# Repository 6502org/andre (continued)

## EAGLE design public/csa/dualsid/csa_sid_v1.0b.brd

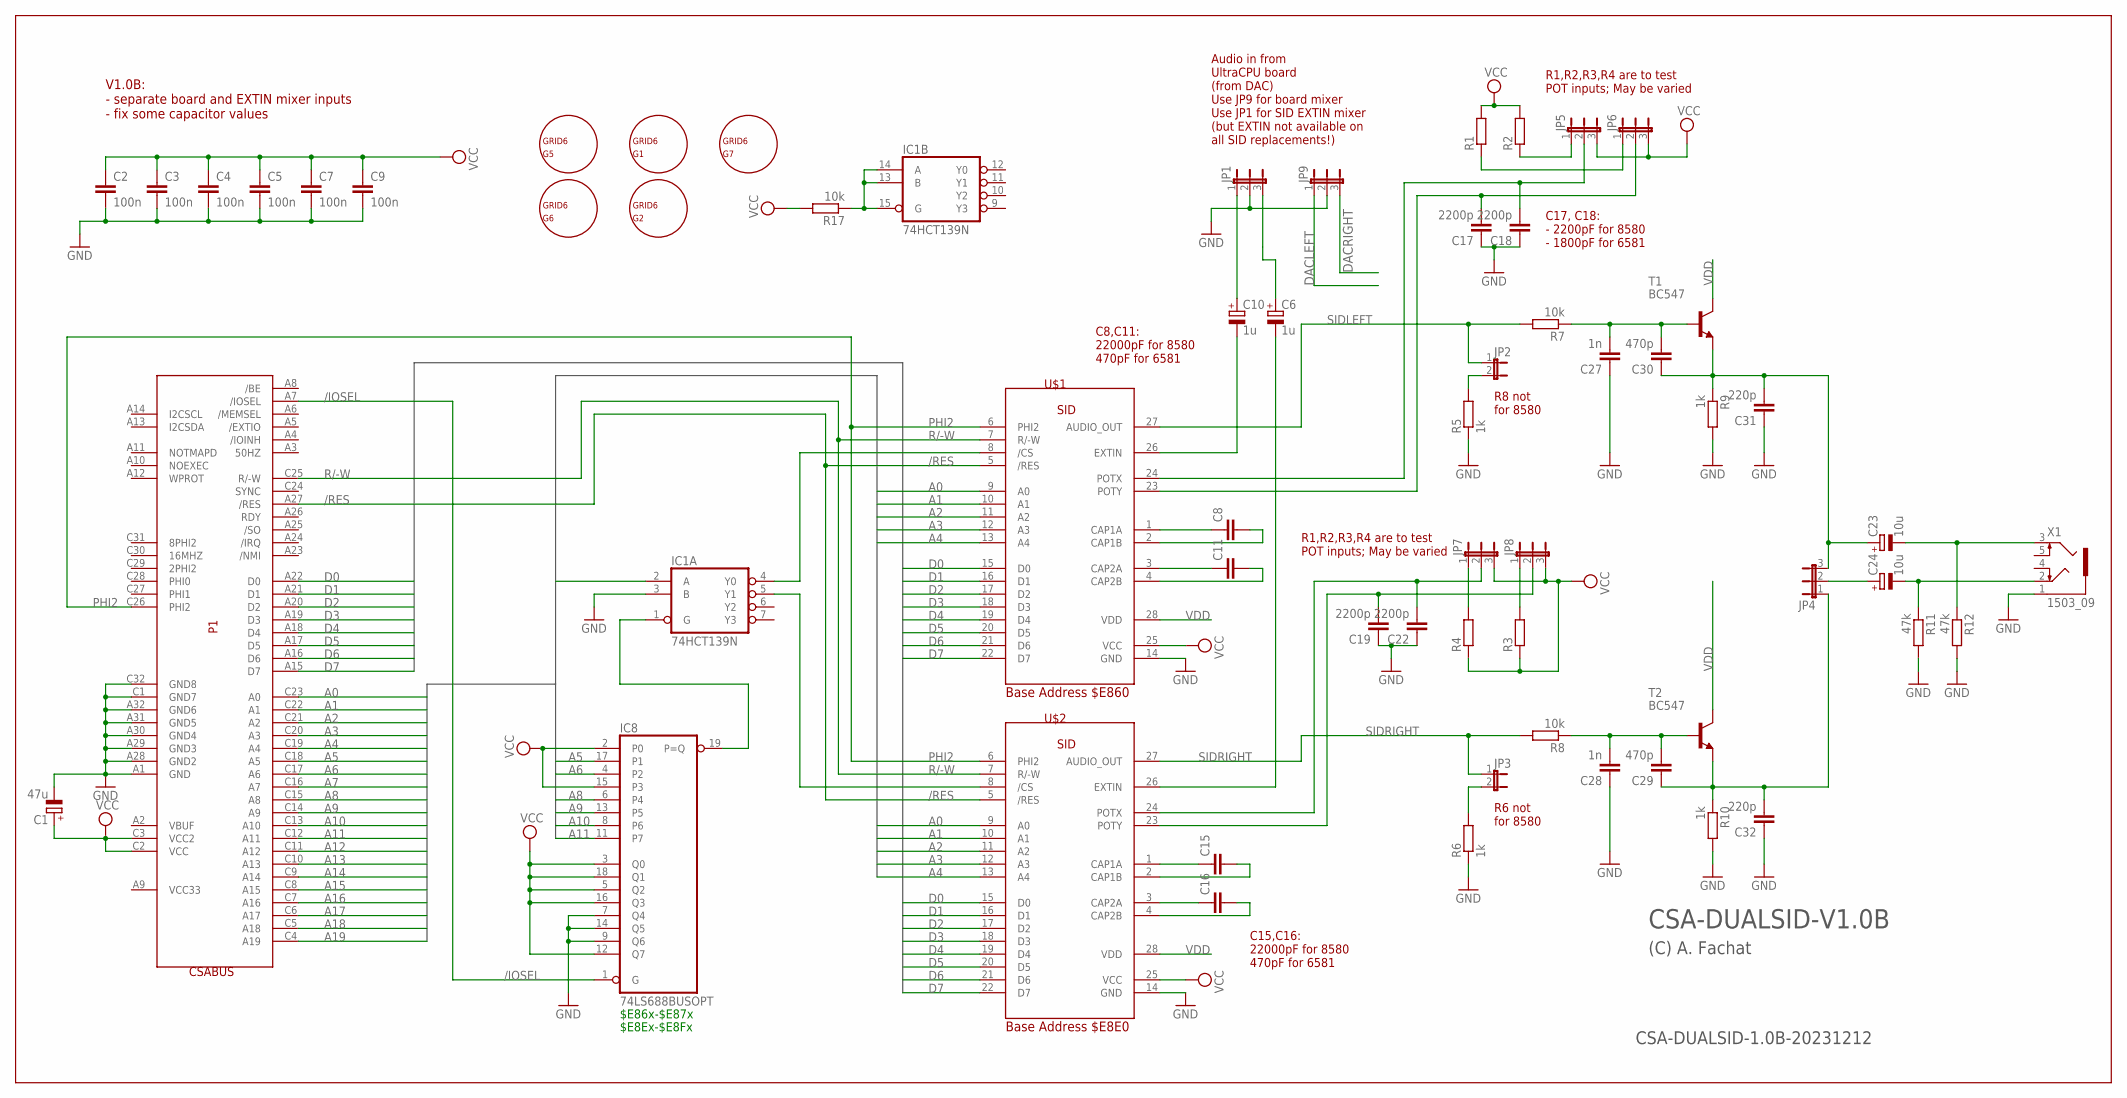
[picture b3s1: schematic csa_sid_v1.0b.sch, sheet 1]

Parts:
C1: 47u; E2,5-7
C2, C3, C4, C5, C7, C9: 100n; C025-025X050
C6, C10: 1u; E2-5
C8, C11, C15, C16: C-EU025-025X050; C025-025X050
C17, C18, C19, C22: 2200p; C025-025X050
C23, C24: 10u; E2-5
C27, C28: 1n; C025-025X050
C29, C30: 470p; C025-025X050
C31, C32: 220p; C025-025X050
G1, G2, G5, G6, G7: GRID6
IC1: 74HCT139N; DIL16
IC8: 74LS688BUSOPT; DIL20
JP1, JP4, JP5, JP6, JP7, JP8, JP9: JP2E; JP2
JP2, JP3: JP1E; JP1
P1: CSABUS
R1, R2, R3, R4: R-EU_0204/7; 0204/7
R5, R6, R9, R10: 1k; 0204/7
R7, R8, R17: 10k; 0204/7
R11, R12: 47k; 0204/7
T1, T2: BC547; TO92
U$1, U$2: SID; DIL28
X1: 1503_09

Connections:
/IOSEL: IC8.1 (G), P1.A7 (/IOSEL)
/RES: P1.A27 (/RES), U$1.5 (/RES), U$2.5 (/RES)
A0: P1.C23 (A0), U$1.9 (A0), U$2.9 (A0)
A1: P1.C22 (A1), U$1.10 (A1), U$2.10 (A1)
A2: P1.C21 (A2), U$1.11 (A2), U$2.11 (A2)
A3: P1.C20 (A3), U$1.12 (A3), U$2.12 (A3)
A4: P1.C19 (A4), U$1.13 (A4), U$2.13 (A4)
A5: IC8.17 (P1), P1.C18 (A5)
A6: IC8.4 (P2), P1.C17 (A6)
A7: IC1.2 (A), P1.C16 (A7)
A8: IC8.6 (P4), P1.C15 (A8)
A9: IC8.13 (P5), P1.C14 (A9)
A10: IC8.8 (P6), P1.C13 (A10)
A11: IC8.11 (P7), P1.C12 (A11)
A12: P1.C11 (A12)
A13: P1.C10 (A13)
A14: P1.C9 (A14)
A15: P1.C8 (A15)
A16: P1.C7 (A16)
A17: P1.C6 (A17)
A18: P1.C5 (A18)
A19: P1.C4 (A19)
D0: P1.A22 (D0), U$1.15 (D0), U$2.15 (D0)
D1: P1.A21 (D1), U$1.16 (D1), U$2.16 (D1)
D2: P1.A20 (D2), U$1.17 (D2), U$2.17 (D2)
D3: P1.A19 (D3), U$1.18 (D3), U$2.18 (D3)
D4: P1.A18 (D4), U$1.19 (D4), U$2.19 (D4)
D5: P1.A17 (D5), U$1.20 (D5), U$2.20 (D5)
D6: P1.A16 (D6), U$1.21 (D6), U$2.21 (D6)
D7: P1.A15 (D7), U$1.22 (D7), U$2.22 (D7)
DACLEFT: JP9.1; also elsewhere on the board
DACRIGHT: JP9.3; also elsewhere on the board
GND: C1.-, C2.2, C3.2, C4.2, C5.2, C7.2, C9.2, C17.1, C18.1, C19.1, C22.1, C27.1, C28.1, C31.1, C32.1, IC1.3 (B), IC1.8 (GND), IC8.7 (Q4), IC8.9 (Q6), IC8.10 (GND), IC8.14 (Q5), JP1.2, JP9.2, P1.A1 (GND), P1.A28 (GND2), P1.A29 (GND3), P1.A30 (GND4), P1.A31 (GND5), P1.A32 (GND6), P1.C1 (GND7), P1.C32 (GND8), R5.1, R6.1, R9.2, R10.2, R11.2, R12.2, U$1.14 (GND), U$2.14 (GND), X1.1; also elsewhere on the board
unnamed: IC1.1 (G), IC8.19 (P=Q)
unnamed: IC1.4 (Y0), U$1.8 (/CS)
unnamed: IC1.5 (Y1), U$2.8 (/CS)
unnamed: C8.1, U$1.1 (CAP1A)
unnamed: C11.1, U$1.3 (CAP2A)
unnamed: C8.2, U$1.2 (CAP1B)
unnamed: C11.2, U$1.4 (CAP2B)
unnamed: C15.1, U$2.1 (CAP1A)
unnamed: C16.1, U$2.3 (CAP2A)
unnamed: C15.2, U$2.2 (CAP1B)
unnamed: C16.2, U$2.4 (CAP2B)
unnamed: C17.2, JP6.2, U$1.23 (POTY)
unnamed: C18.2, JP5.2, U$1.24 (POTX)
unnamed: C19.2, JP8.2, U$2.23 (POTY)
unnamed: C22.2, JP7.2, U$2.24 (POTX)
unnamed: C10.-, U$1.26 (EXTIN)
unnamed: JP5.1, R2.1
unnamed: JP6.1, R1.1
unnamed: JP3.2, R6.2
unnamed: JP2.2, R5.2
unnamed: C6.-, U$2.26 (EXTIN)
unnamed: C23.-, R12.1, X1.3
unnamed: C24.-, R11.1, X1.2
unnamed: C29.1, C32.2, JP4.1, R10.1, T2.1 (E)
unnamed: C23.+, C30.1, C31.2, JP4.3, R9.1, T1.1 (E)
unnamed: C27.2, C30.2, R7.1, T1.2 (B)
unnamed: C28.2, C29.2, R8.1, T2.2 (B)
unnamed: C24.+, JP4.2
unnamed: IC1.13 (B), IC1.14 (A), IC1.15 (G), R17.1
unnamed: JP7.1, R4.2
unnamed: JP8.1, R3.2
unnamed: C6.+, JP1.3
unnamed: C10.+, JP1.1
PHI2: P1.C26 (PHI2), U$1.6 (PHI2), U$2.6 (PHI2)
R/-W: P1.C25 (R/-W), U$1.7 (R/-W), U$2.7 (R/-W)
SIDLEFT: JP2.1, R7.2, U$1.27 (AUDIO_OUT); also elsewhere on the board
SIDRIGHT: JP3.1, R8.2, U$2.27 (AUDIO_OUT); also elsewhere on the board
VCC: C1.+, C2.1, C3.1, C4.1, C5.1, C7.1, C9.1, IC1.16 (VCC), IC8.2 (P0), IC8.3 (Q0), IC8.5 (Q2), IC8.12 (Q7), IC8.15 (P3), IC8.16 (Q3), IC8.18 (Q1), IC8.20 (VCC), JP5.3, JP6.3, JP7.3, JP8.3, P1.C2 (VCC), P1.C3 (VCC2), R1.2, R2.2, R3.1, R4.1, R17.2, U$1.25 (VCC), U$2.25 (VCC); also elsewhere on the board
VDD: T1.3 (C), T2.3 (C), U$1.28 (VDD), U$2.28 (VDD); also elsewhere on the board

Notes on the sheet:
CSA-DUALSID-V1.0B
(C) A. Fachat
CSA-DUALSID-1.0B-20231212
$E86x-$E87x
$E8Ex-$E8Fx
Audio in from UltraCPU board (from DAC) Use JP9 for board mixer Use JP1 for SID EXTIN mixer (but EXTIN not available on all SID replacements!)
R8 not for 8580
R6 not for 8580
C8,C11: 22000pF for 8580 470pF for 6581
C15,C16: 22000pF for 8580 470pF for 6581
R1,R2,R3,R4 are to test POT inputs; May be varied
C17, C18: - 2200pF for 8580 - 1800pF for 6581
V1.0B: - separate board and EXTIN mixer inputs - fix some capacitor values
Base Address $E860
Base Address $E8E0

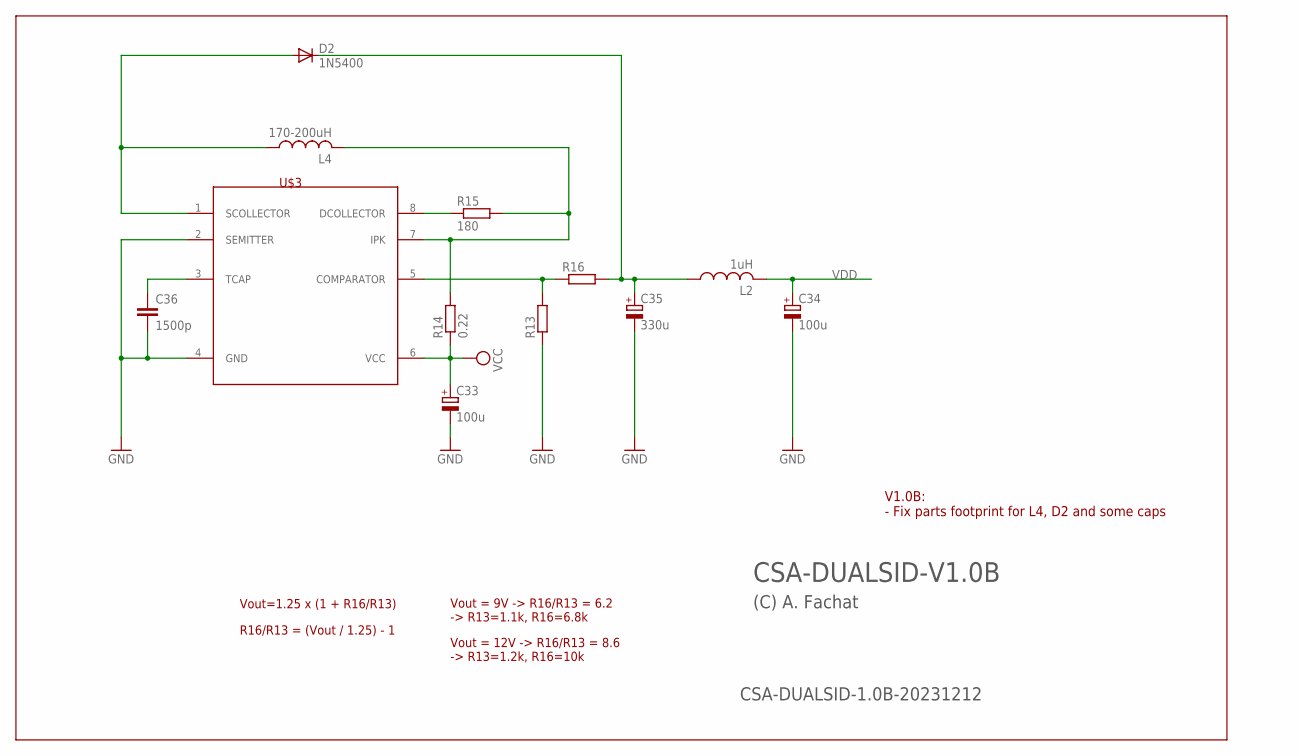
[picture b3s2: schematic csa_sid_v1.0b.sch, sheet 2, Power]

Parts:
C33, C34: 100u; E2,5-7
C35: 330u; E2,5-7
C36: 1500p; C025-024X044
D2: 1N5400; DO201-15
L2: 1uH; 0204/7
L4: 170-200uH; TJ4-U2
R13, R16: R-EU_0204/7; 0204/7
R14: 0.22; 0204/7
R15: 180; 0204/7
U$3: MC34063A; DIL08

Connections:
GND: C33.-, C34.-, C35.-, C36.2, R13.1, U$3.2 (SEMITTER), U$3.4 (GND); also elsewhere on the board
unnamed: C36.1, U$3.3 (TCAP)
unnamed: R13.2, R16.1, U$3.5 (COMPARATOR)
unnamed: D2.A, L4.1, U$3.1 (SCOLLECTOR)
unnamed: C35.+, D2.C, L2.1, R16.2
unnamed: L4.2, R14.2, R15.2, U$3.7 (IPK)
unnamed: R15.1, U$3.8 (DCOLLECTOR)
VCC: C33.+, R14.1, U$3.6 (VCC); also elsewhere on the board
VDD: C34.+, L2.2; also elsewhere on the board

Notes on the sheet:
Vout=1.25 x (1 + R16/R13)
R16/R13 = (Vout / 1.25) - 1
Vout = 9V -> R16/R13 = 6.2 -> R13=1.1k, R16=6.8k
Vout = 12V -> R16/R13 = 8.6 -> R13=1.2k, R16=10k
CSA-DUALSID-V1.0B
(C) A. Fachat
CSA-DUALSID-1.0B-20231212
V1.0B: - Fix parts footprint for L4, D2 and some caps

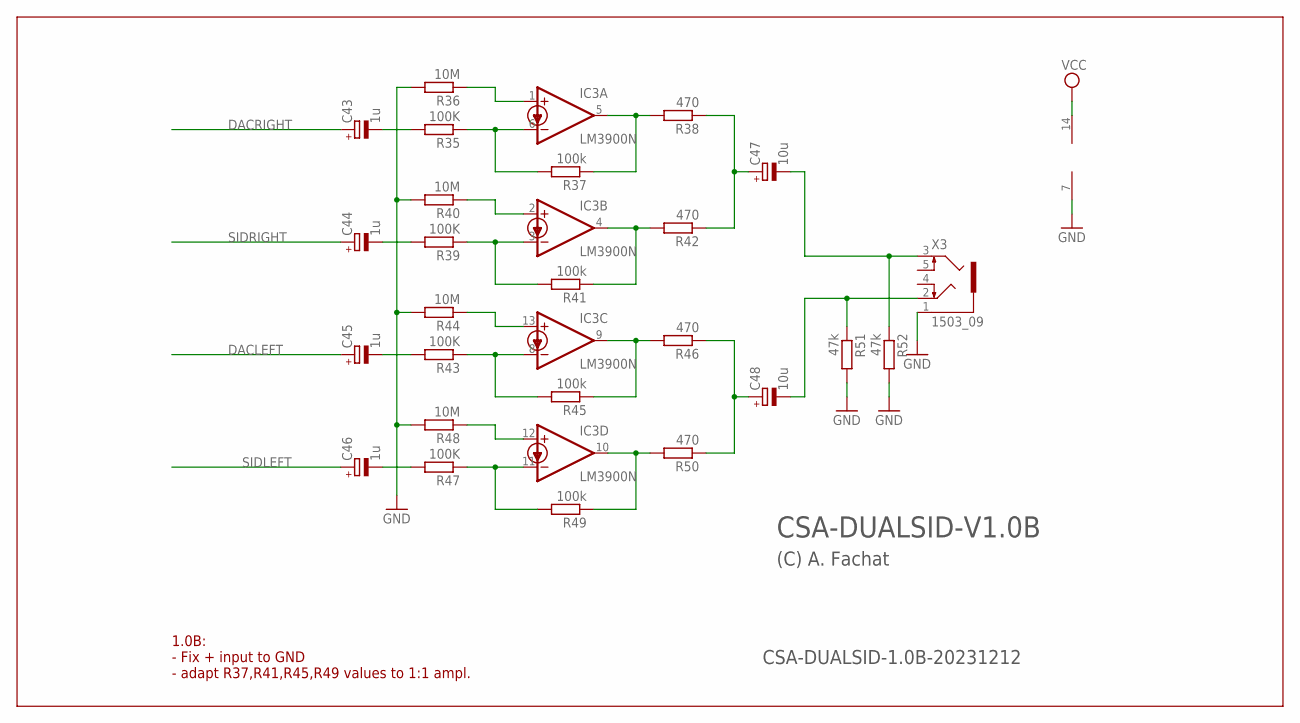
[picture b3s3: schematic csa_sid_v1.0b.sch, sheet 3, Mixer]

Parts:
C43, C44, C45, C46: 1u; E2-5
C47, C48: 10u; E2-5
IC3: LM3900N; DIL14
R35, R39, R43, R47: 100K; 0204/7
R36, R40, R44, R48: 10M; 0204/7
R37, R41, R45, R49: 100k; 0204/7
R38, R42, R46, R50: 470; 0204/7
R51, R52: 47k; 0204/7
X3: 1503_09

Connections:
DACLEFT: C45.+; also elsewhere on the board
DACRIGHT: C43.+; also elsewhere on the board
GND: IC3.7 (GND), R36.2, R40.2, R44.2, R48.2, R51.2, R52.2, X3.1; also elsewhere on the board
unnamed: IC3.1 (+IN), R36.1
unnamed: C43.-, R35.2
unnamed: IC3.6 (-IN), R35.1, R37.2
unnamed: IC3.5 (OUT), R37.1, R38.2
unnamed: IC3.2 (+IN), R40.1
unnamed: C44.-, R39.2
unnamed: IC3.3 (-IN), R39.1, R41.2
unnamed: IC3.4 (OUT), R41.1, R42.2
unnamed: IC3.13 (+IN), R44.1
unnamed: C45.-, R43.2
unnamed: IC3.8 (-IN), R43.1, R45.2
unnamed: IC3.9 (OUT), R45.1, R46.2
unnamed: IC3.12 (+IN), R48.1
unnamed: C46.-, R47.2
unnamed: IC3.11 (-IN), R47.1, R49.2
unnamed: IC3.10 (OUT), R49.1, R50.2
unnamed: C47.+, R38.1, R42.1
unnamed: C47.-, R52.1, X3.3
unnamed: C48.+, R46.1, R50.1
unnamed: C48.-, R51.1, X3.2
SIDLEFT: C46.+; also elsewhere on the board
SIDRIGHT: C44.+; also elsewhere on the board
VCC: IC3.14 (V+); also elsewhere on the board

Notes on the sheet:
CSA-DUALSID-V1.0B
(C) A. Fachat
CSA-DUALSID-1.0B-20231212
1.0B: - Fix + input to GND - adapt R37,R41,R45,R49 values to 1:1 ampl.

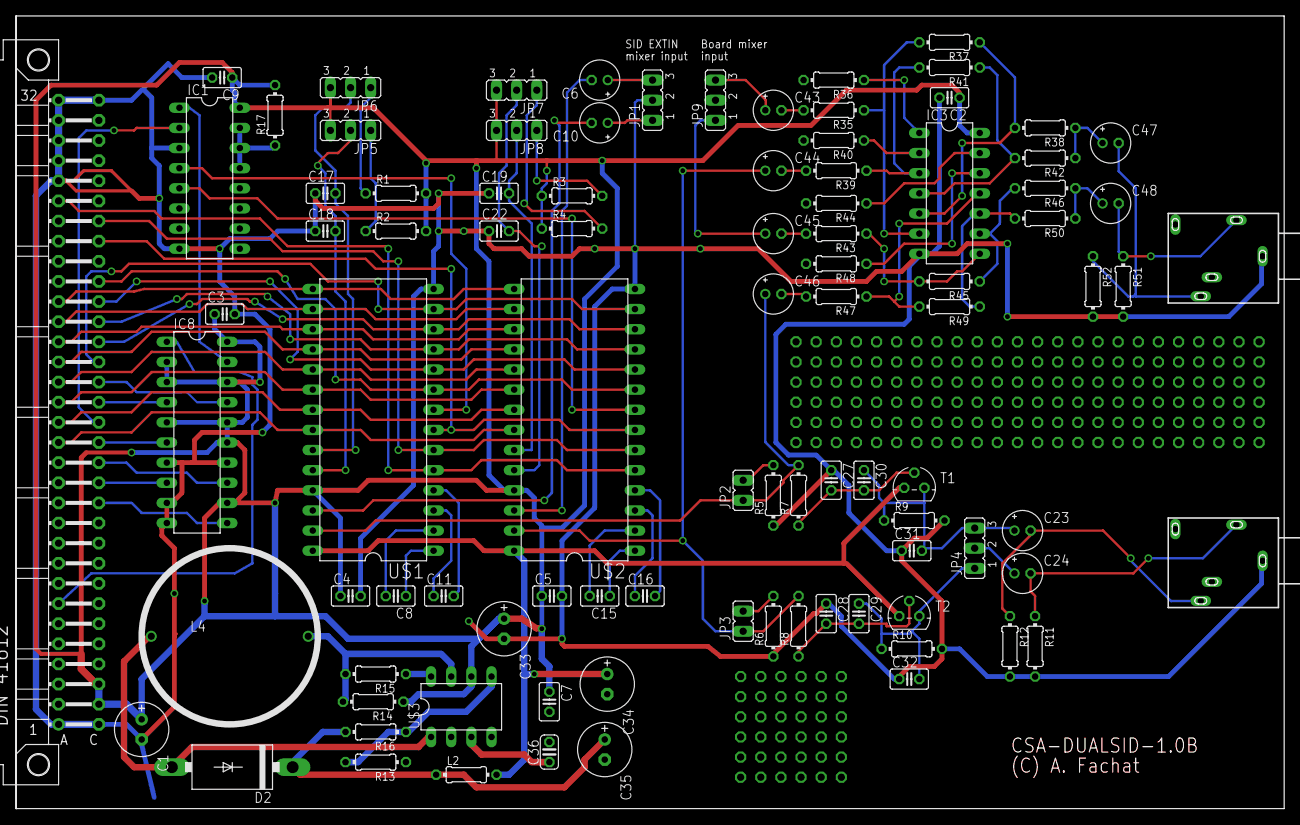
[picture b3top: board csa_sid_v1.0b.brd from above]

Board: 2 copper layers, 160.0 x 100.0 mm, 98 parts (0 on the bottom side), 90 nets.

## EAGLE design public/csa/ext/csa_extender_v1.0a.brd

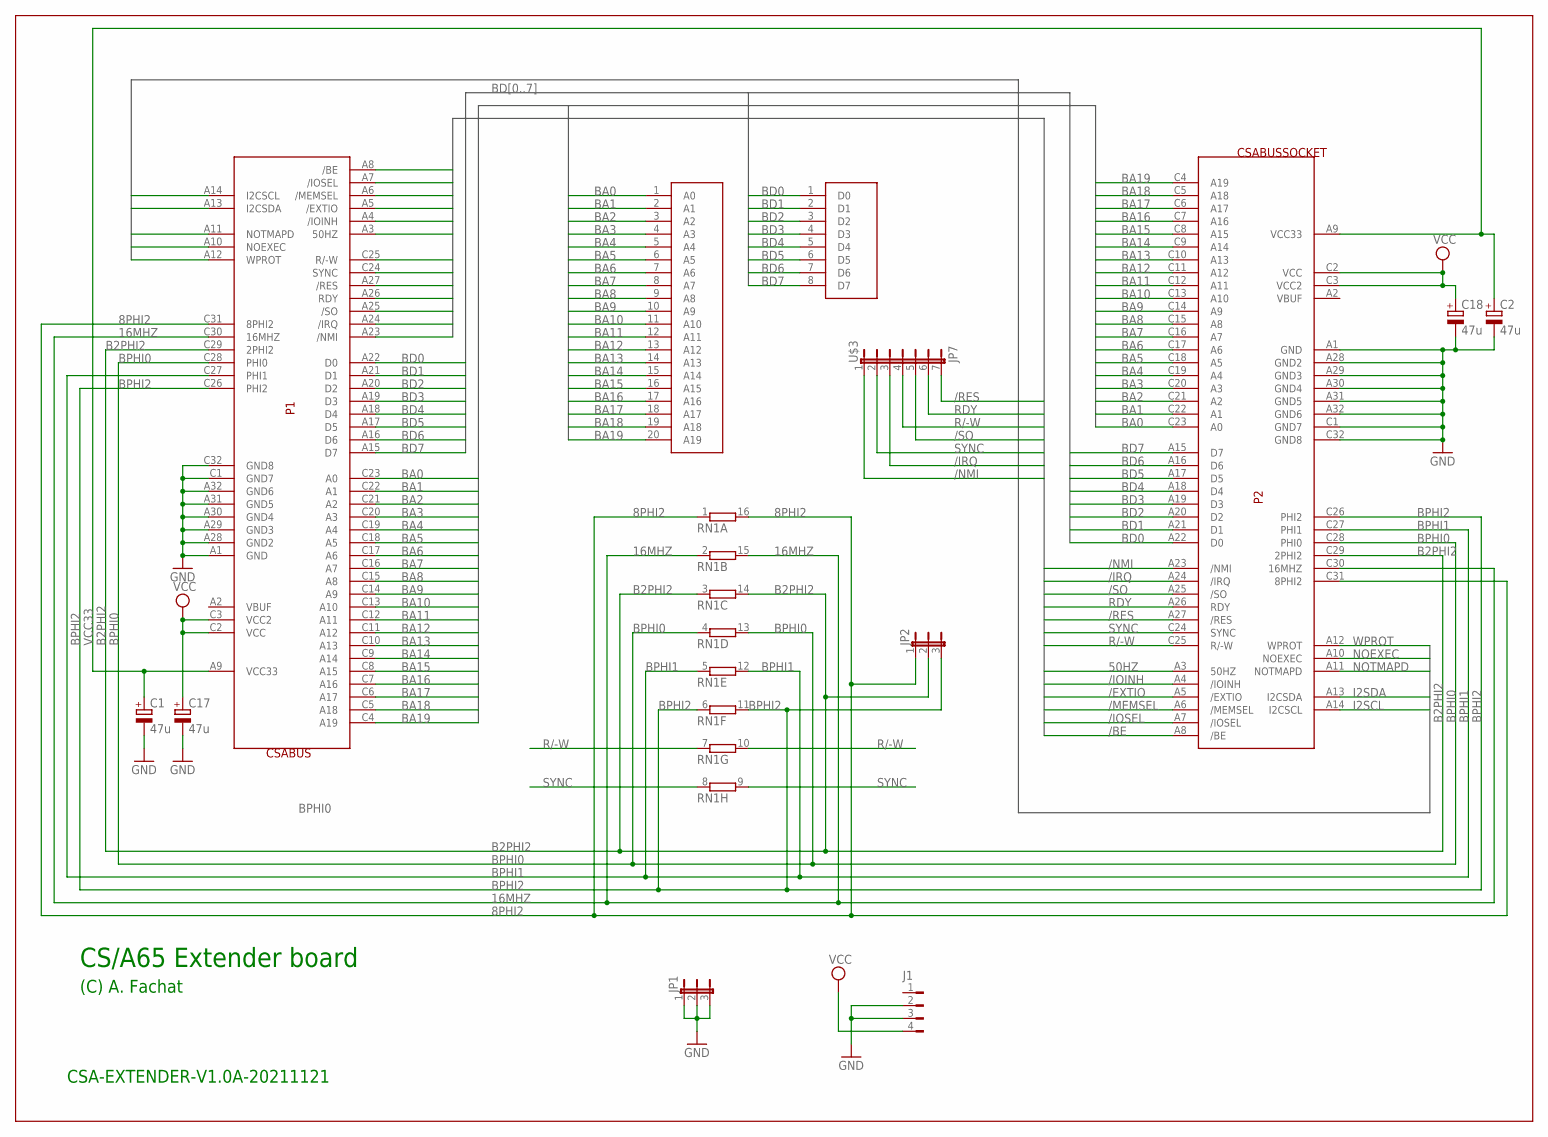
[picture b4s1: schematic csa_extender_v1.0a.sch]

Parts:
C1, C2, C17, C18: 47u; E2,5-5
J1: FLOP-4W827001; 827001
JP1, JP2: JP2E; JP2
P1: CSABUS
P2: CSABUSSOCKET; CSABUSSOCK
RN1: 8R-N; DIL16
U$1: JA0-19; A0-19
U$2: JD0-7; D0-7
U$3: JP7

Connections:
8PHI2: JP2.1, P1.C31 (8PHI2), P2.C31 (8PHI2), RN1.1, RN1.16 (2)
16MHZ: P1.C30 (16MHZ), P2.C30 (16MHZ), RN1.2 (1), RN1.15 (2)
50HZ: P1.A3 (50HZ), P2.A3 (50HZ)
/BE: P1.A8 (/BE), P2.A8 (/BE)
/EXTIO: P1.A5 (/EXTIO), P2.A5 (/EXTIO)
/IOINH: P1.A4 (/IOINH), P2.A4 (/IOINH)
/IOSEL: P1.A7 (/IOSEL), P2.A7 (/IOSEL)
/IRQ: P1.A24 (/IRQ), P2.A24 (/IRQ), U$3.3
/MEMSEL: P1.A6 (/MEMSEL), P2.A6 (/MEMSEL)
/NMI: P1.A23 (/NMI), P2.A23 (/NMI), U$3.1
/RES: P1.A27 (/RES), P2.A27 (/RES), U$3.7
/SO: P1.A25 (/SO), P2.A25 (/SO), U$3.5
B2PHI2: JP2.2, P1.C29 (2PHI2), P2.C29 (2PHI2), RN1.3 (1), RN1.14 (2)
BA0: P1.C23 (A0), P2.C23 (A0), U$1.1 (A0)
BA1: P1.C22 (A1), P2.C22 (A1), U$1.2 (A1)
BA2: P1.C21 (A2), P2.C21 (A2), U$1.3 (A2)
BA3: P1.C20 (A3), P2.C20 (A3), U$1.4 (A3)
BA4: P1.C19 (A4), P2.C19 (A4), U$1.5 (A4)
BA5: P1.C18 (A5), P2.C18 (A5), U$1.6 (A5)
BA6: P1.C17 (A6), P2.C17 (A6), U$1.7 (A6)
BA7: P1.C16 (A7), P2.C16 (A7), U$1.8 (A7)
BA8: P1.C15 (A8), P2.C15 (A8), U$1.9 (A8)
BA9: P1.C14 (A9), P2.C14 (A9), U$1.10 (A9)
BA10: P1.C13 (A10), P2.C13 (A10), U$1.11 (A10)
BA11: P1.C12 (A11), P2.C12 (A11), U$1.12 (A11)
BA12: P1.C11 (A12), P2.C11 (A12), U$1.13 (A12)
BA13: P1.C10 (A13), P2.C10 (A13), U$1.14 (A13)
BA14: P1.C9 (A14), P2.C9 (A14), U$1.15 (A14)
BA15: P1.C8 (A15), P2.C8 (A15), U$1.16 (A15)
BA16: P1.C7 (A16), P2.C7 (A16), U$1.17 (A16)
BA17: P1.C6 (A17), P2.C6 (A17), U$1.18 (A17)
BA18: P1.C5 (A18), P2.C5 (A18), U$1.19 (A18)
BA19: P1.C4 (A19), P2.C4 (A19), U$1.20 (A19)
BD0: P1.A22 (D0), P2.A22 (D0), U$2.1 (D0)
BD1: P1.A21 (D1), P2.A21 (D1), U$2.2 (D1)
BD2: P1.A20 (D2), P2.A20 (D2), U$2.3 (D2)
BD3: P1.A19 (D3), P2.A19 (D3), U$2.4 (D3)
BD4: P1.A18 (D4), P2.A18 (D4), U$2.5 (D4)
BD5: P1.A17 (D5), P2.A17 (D5), U$2.6 (D5)
BD6: P1.A16 (D6), P2.A16 (D6), U$2.7 (D6)
BD7: P1.A15 (D7), P2.A15 (D7), U$2.8 (D7)
BPHI0: P1.C28 (PHI0), P2.C28 (PHI0), RN1.4 (1), RN1.13 (2)
BPHI1: P1.C27 (PHI1), P2.C27 (PHI1), RN1.5 (1), RN1.12 (2)
BPHI2: JP2.3, P1.C26 (PHI2), P2.C26 (PHI2), RN1.6 (1), RN1.11 (2)
GND: C1.-, C2.-, C17.-, C18.-, J1.2, J1.3, JP1.1, JP1.2, JP1.3, P1.A1 (GND), P1.A28 (GND2), P1.A29 (GND3), P1.A30 (GND4), P1.A31 (GND5), P1.A32 (GND6), P1.C1 (GND7), P1.C32 (GND8), P2.A1 (GND), P2.A28 (GND2), P2.A29 (GND3), P2.A30 (GND4), P2.A31 (GND5), P2.A32 (GND6), P2.C1 (GND7), P2.C32 (GND8)
I2SCL: P1.A14 (I2CSCL), P2.A14 (I2CSCL)
I2SDA: P1.A13 (I2CSDA), P2.A13 (I2CSDA)
NOEXEC: P1.A10 (NOEXEC), P2.A10 (NOEXEC)
NOTMAPD: P1.A11 (NOTMAPD), P2.A11 (NOTMAPD)
R/-W: P1.C25 (R/-W), P2.C25 (R/-W), RN1.7 (1), RN1.10 (2), U$3.4
RDY: P1.A26 (RDY), P2.A26 (RDY), U$3.6
SYNC: P1.C24 (SYNC), P2.C24 (SYNC), RN1.8 (1), RN1.9 (2), U$3.2
VCC: C17.+, C18.+, J1.4, P1.C2 (VCC), P1.C3 (VCC2), P2.C2 (VCC), P2.C3 (VCC2)
VCC33: C1.+, C2.+, P1.A9 (VCC33), P2.A9 (VCC33)
WPROT: P1.A12 (WPROT), P2.A12 (WPROT)

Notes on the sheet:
CSA-EXTENDER-V1.0A-20211121
CS/A65 Extender board
(C) A. Fachat

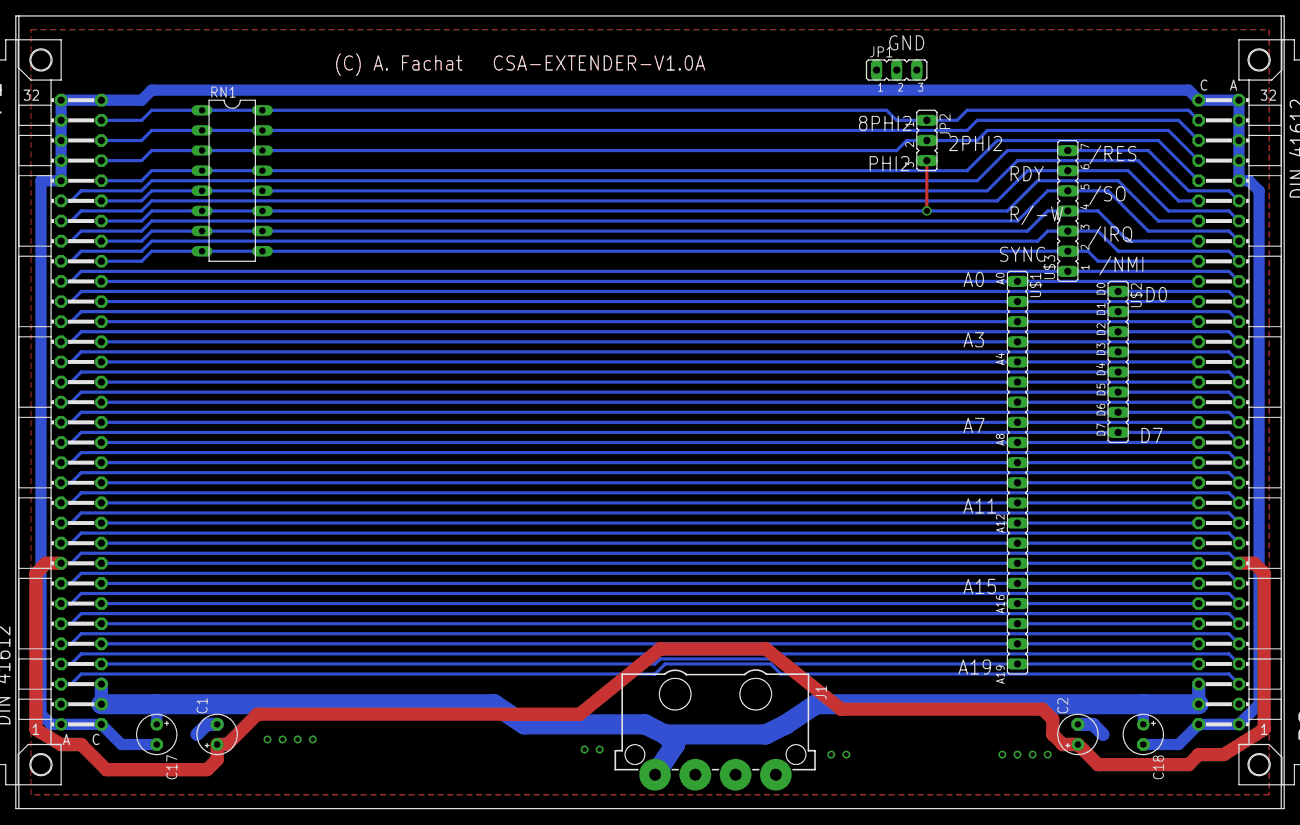
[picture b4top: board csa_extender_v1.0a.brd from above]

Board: 2 copper layers, 160.0 x 100.0 mm, 13 parts (0 on the bottom side), 55 nets.

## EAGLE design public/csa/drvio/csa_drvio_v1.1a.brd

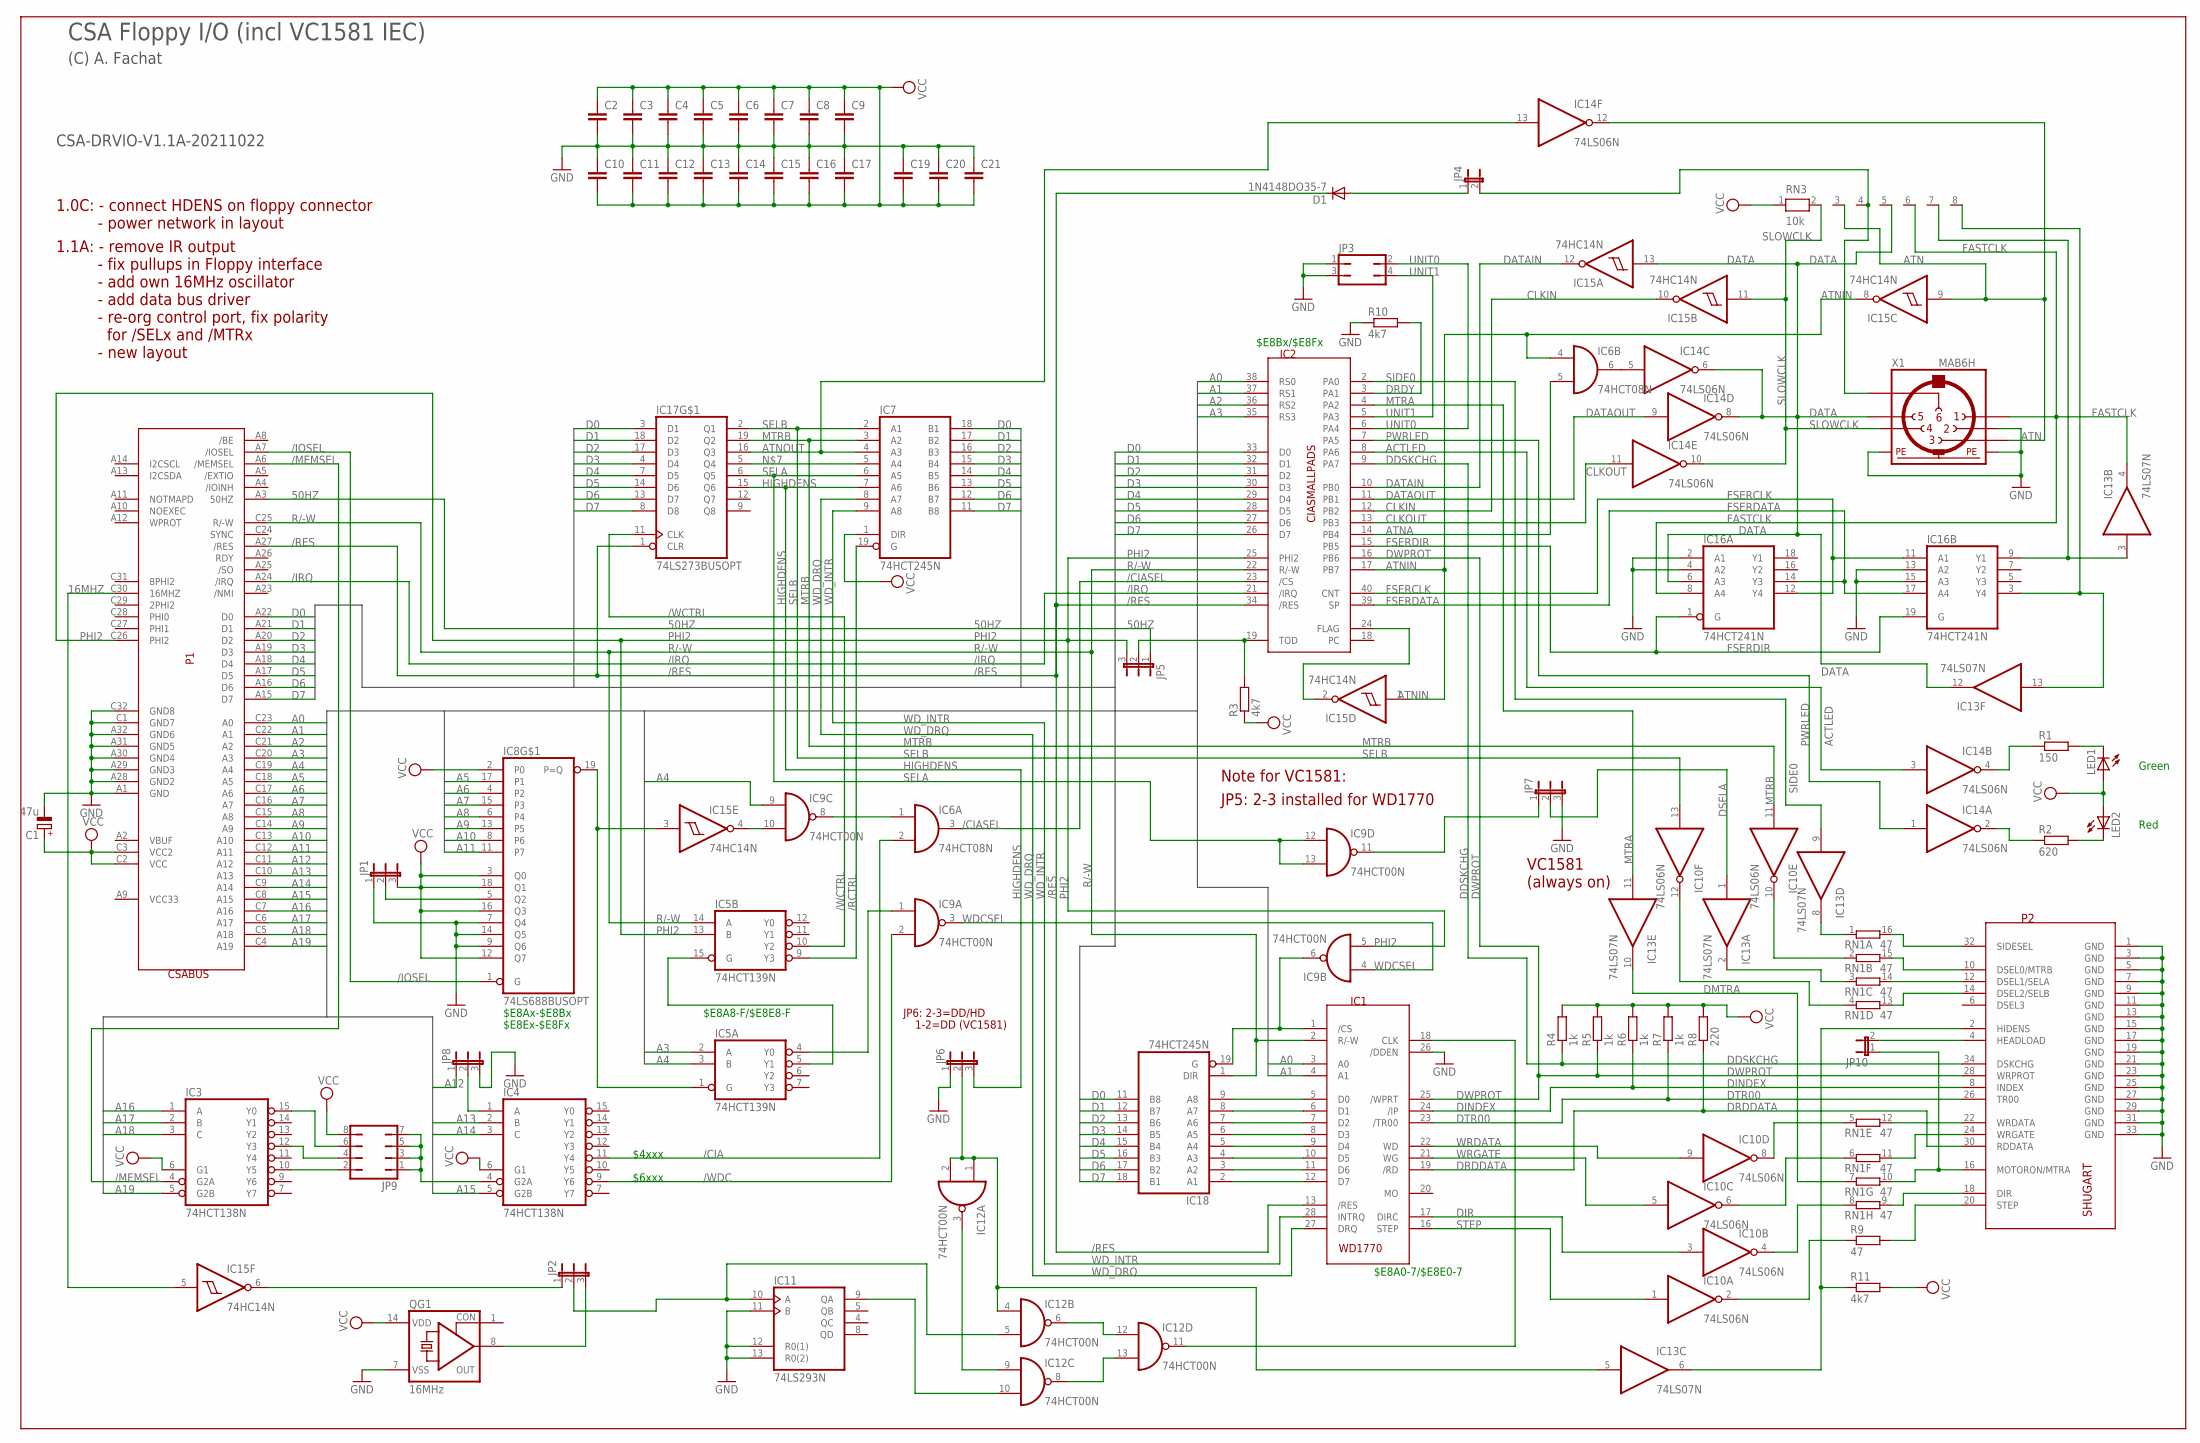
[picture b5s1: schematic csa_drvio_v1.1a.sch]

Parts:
C1: 47u; E2,5-5
C2, C3, C4, C5, C6, C7, C8, C9, C10, C11, C12, C13, C14, C15, C16, C17, C19, C20, C21: C-EU025-025X050; C025-025X050
D1: 1N4148DO35-7; DO35-7
IC1: WD1770; DIL28
IC2: CIASMALLPADS; DIP40
IC3, IC4: 74HCT138N; DIL16
IC5: 74HCT139N; DIL16
IC6: 74HCT08N; DIL14
IC7, IC18: 74HCT245N; DIL20
IC8: 74LS688BUSOPT; DIL20
IC9, IC12: 74HCT00N; DIL14
IC10, IC14: 74LS06N; DIL14
IC11: 74LS293N; DIL14
IC13: 74LS07N; DIL14
IC15: 74HC14N; DIL14
IC16: 74HCT241N; DIL20
IC17: 74LS273BUSOPT; DIL20
JP1, JP2, JP5, JP6, JP7, JP8: JP2E; JP2
JP3: JP2Q
JP4, JP10: JP1E; JP1
JP9: JP4Q
LED1, LED2: LED5MM
P1: CSABUS
P2: SHUGART; CON34
QG1: 16MHz; SG51
R1: 150; 0207/10
R2: 620; 0207/10
R3: 4k7; 0204/7
R4, R5, R6, R7: 1k; 0207/10
R8: 220; 0207/10
R9: 47; 0207/10
R10, R11: 4k7; 0207/10
RN1: 47; DIL16
RN3: 10k; RN-8
X1: MAB6H

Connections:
16MHZ: IC15.5 (I), P1.C30 (16MHZ)
50HZ: JP5.1, P1.A3 (50HZ)
/CIA: IC4.11 (Y4), IC6.2 (I1)
/CIASEL: IC2.23 (/CS), IC6.3 (O)
/IOSEL: IC8.1 (G), P1.A7 (/IOSEL)
/IRQ: IC2.21 (/IRQ), P1.A24 (/IRQ)
/MEMSEL: IC3.4 (G2A), P1.A6 (/MEMSEL)
/RCTRL: IC5.9 (Y3), IC7.19 (G)
/RES: D1.C, IC1.13 (/RES), IC2.34 (/RES), IC17.1 (CLR), P1.A27 (/RES)
/WCTRL: IC5.10 (Y2), IC17.11 (CLK)
/WDC: IC4.9 (Y6), IC9.2 (I1)
A0: IC1.3 (A0), IC2.38 (RS0), P1.C23 (A0)
A1: IC1.4 (A1), IC2.37 (RS1), P1.C22 (A1)
A2: IC2.36 (RS2), P1.C21 (A2)
A3: IC2.35 (RS3), IC5.2 (A), P1.C20 (A3)
A4: IC5.3 (B), IC9.9 (I0), P1.C19 (A4)
A5: IC8.17 (P1), P1.C18 (A5)
A6: IC8.4 (P2), P1.C17 (A6)
A7: IC8.15 (P3), P1.C16 (A7)
A8: IC8.6 (P4), P1.C15 (A8)
A9: IC8.13 (P5), P1.C14 (A9)
A10: IC8.8 (P6), P1.C13 (A10)
A11: IC8.11 (P7), P1.C12 (A11)
A12: JP8.1, P1.C11 (A12)
A13: IC4.2 (B), P1.C10 (A13)
A14: IC4.3 (C), P1.C9 (A14)
A15: IC4.5 (G2B), P1.C8 (A15)
A16: IC3.1 (A), P1.C7 (A16)
A17: IC3.2 (B), P1.C6 (A17)
A18: IC3.3 (C), P1.C5 (A18)
A19: IC3.5 (G2B), P1.C4 (A19)
ACTLED: IC2.8 (PA6), IC14.3 (I)
ATN: IC14.12 (O), IC15.9 (I), RN3.3, X1.3
ATNA: IC2.14 (PB4), IC6.5 (I1)
ATNIN: IC2.17 (PB7), IC6.4 (I0), IC15.1 (I), IC15.8 (O)
ATNOUT: IC7.4 (A3), IC14.13 (I), IC17.16 (Q3)
CLKIN: IC2.12 (PB2), IC15.10 (O)
CLKOUT: IC2.13 (PB3), IC14.11 (I)
D0: IC2.33 (D0), IC7.18 (B1), IC17.3 (D1), IC18.11 (B8), P1.A22 (D0)
D1: IC2.32 (D1), IC7.17 (B2), IC17.18 (D2), IC18.12 (B7), P1.A21 (D1)
D2: IC2.31 (D2), IC7.16 (B3), IC17.17 (D3), IC18.13 (B6), P1.A20 (D2)
D3: IC2.30 (D3), IC7.15 (B4), IC17.4 (D4), IC18.14 (B5), P1.A19 (D3)
D4: IC2.29 (D4), IC7.14 (B5), IC17.7 (D5), IC18.15 (B4), P1.A18 (D4)
D5: IC2.28 (D5), IC7.13 (B6), IC17.14 (D6), IC18.16 (B3), P1.A17 (D5)
D6: IC2.27 (D6), IC7.12 (B7), IC17.13 (D7), IC18.17 (B2), P1.A16 (D6)
D7: IC2.26 (D7), IC7.11 (B8), IC17.8 (D8), IC18.18 (B1), P1.A15 (D7)
DATA: IC13.12 (O), IC14.6 (O), IC14.8 (O), IC15.13 (I), IC16.6 (A3), RN3.5, X1.5
DATAIN: IC2.10 (PB0), IC15.12 (O)
DATAOUT: IC2.11 (PB1), IC14.9 (I)
DDSKCHG: IC2.9 (PA7), P2.34 (DSKCHG), R4.1
DINDEX: IC1.24 (/IP), P2.8 (INDEX), R6.1
DIR: IC1.17 (DIRC), IC10.3 (I)
DMTRA: IC13.10 (O), RN1.7 (1)
DMTRB: IC10.10 (O), RN1.2 (1)
DRDDATA: IC1.19 (/RD), P2.30 (RDDATA), R8.1
DRDY: IC2.3 (PA1), R10.2
DSELA: IC13.1 (I), JP7.2
DTR00: IC1.23 (/TR00), P2.26 (TR00), R7.1
DWPROT: IC1.25 (/WPRT), IC2.16 (PB6), P2.28 (WRPROT), R5.1
FASTCLK: IC13.4 (O), IC16.8 (A4), RN3.6, X1.1
FSERCLK: IC2.40 (CNT), IC16.11 (A1), IC16.12 (Y4)
FSERDATA: IC2.39 (SP), IC16.14 (Y3), IC16.17 (A4)
FSERDIR: IC2.15 (PB5), IC16.1 (G), IC16.19 (G)
GND: C1.-, C2.2, C3.2, C4.2, C5.2, C6.2, C7.2, C8.2, C9.2, C10.1, C11.1, C12.1, C13.1, C14.1, C15.1, C16.1, C17.1, C19.1, C20.1, C21.1, IC1.14 (GND), IC1.26 (/DDEN), IC2.1 (GND), IC3.8 (GND), IC4.8 (GND), IC5.8 (GND), IC6.7 (GND), IC7.10 (GND), IC8.7 (Q4), IC8.9 (Q6), IC8.10 (GND), IC8.14 (Q5), IC9.7 (GND), IC10.7 (GND), IC11.7 (GND), IC11.11 (B), IC11.12 (R0(1)), IC11.13 (R0(2)), IC12.7 (GND), IC13.7 (GND), IC14.7 (GND), IC15.7 (GND), IC16.2 (A1), IC16.4 (A2), IC16.10 (GND), IC16.13 (A2), IC16.15 (A3), IC17.10 (GND), IC18.10 (GND), JP1.1, JP3.1, JP3.3, JP6.1, JP7.3, JP8.3, P1.A1 (GND), P1.A28 (GND2), P1.A29 (GND3), P1.A30 (GND4), P1.A31 (GND5), P1.A32 (GND6), P1.C1 (GND7), P1.C32 (GND8), P2.1 (GND), P2.3 (GND), P2.5 (GND), P2.7 (GND), P2.9 (GND), P2.11 (GND), P2.13 (GND), P2.15 (GND), P2.17 (GND), P2.19 (GND), P2.21 (GND), P2.23 (GND), P2.25 (GND), P2.27 (GND), P2.29 (GND), P2.31 (GND), P2.33 (GND), QG1.7 (VSS), R10.1, X1.2, X1.PE, X1.PE@ (PE)
HIGHDENS: IC7.7 (A6), IC17.15 (Q6), JP6.3
MTRA: IC2.4 (PA2), IC13.11 (I)
MTRB: IC7.3 (A2), IC10.11 (I), IC17.19 (Q2)
unnamed: IC3.15 (Y0), JP9.6
unnamed: IC3.10 (Y5), JP9.2
unnamed: IC4.4 (G2A), JP9.1, JP9.3, JP9.5, JP9.7
unnamed: IC5.4 (Y0), IC9.1 (I0)
unnamed: IC3.12 (Y3), JP9.4
unnamed: IC5.1 (G), IC8.19 (P=Q), IC15.3 (I)
unnamed: IC7.5 (A4), IC17.5 (Q4)
unnamed: IC5.5 (Y1), IC5.15 (G)
unnamed: IC13.6 (O), P2.2 (HIDENS), R11.1
unnamed: IC1.1 (/CS), IC9.6 (O), IC18.19 (G)
unnamed: IC8.5 (Q2), JP1.2
unnamed: IC6.1 (I0), IC9.8 (O)
unnamed: JP4.2, RN3.4, X1.6
unnamed: IC9.10 (I1), IC15.4 (O)
unnamed: D1.A, JP4.1
unnamed: IC10.2 (O), R9.1
unnamed: IC10.4 (O), RN1.8 (1)
unnamed: IC12.1 (I0), IC12.2 (I1), IC12.4 (I0), IC13.5 (I), JP6.2
unnamed: IC10.8 (O), RN1.5 (1)
unnamed: IC10.6 (O), RN1.6 (1)
unnamed: IC2.19 (TOD), JP5.2, R3.2
unnamed: IC15.6 (O), JP2.1
unnamed: IC10.12 (O), RN1.4 (1)
unnamed: IC13.2 (O), RN1.3 (1)
unnamed: P2.32 (SIDESEL), RN1.16 (2)
unnamed: JP2.3, QG1.8 (OUT)
unnamed: IC11.10 (A), IC12.5 (I1), JP2.2
unnamed: IC11.9 (QA), IC12.10 (I1)
unnamed: IC12.6 (O), IC12.12 (I0)
unnamed: IC12.8 (O), IC12.13 (I1)
unnamed: IC12.3 (O), IC12.9 (I0)
unnamed: IC13.8 (O), RN1.1
unnamed: IC1.5 (D0), IC18.9 (A8)
unnamed: IC1.6 (D1), IC18.8 (A7)
unnamed: IC1.7 (D2), IC18.7 (A6)
unnamed: IC1.8 (D3), IC18.6 (A5)
unnamed: IC1.9 (D4), IC18.5 (A4)
unnamed: IC1.10 (D5), IC18.4 (A3)
unnamed: IC1.18 (CLK), IC12.11 (O)
unnamed: IC1.11 (D6), IC18.3 (A2)
unnamed: IC1.12 (D7), IC18.2 (A1)
unnamed: JP10.2, P2.4 (HEADLOAD)
unnamed: P2.10 (DSEL0/MTRB), RN1.15 (2)
unnamed: IC14.4 (O), R1.1
unnamed: LED1.K (C), R1.2
unnamed: LED2.K (C), R2.2
unnamed: IC14.2 (O), R2.1
unnamed: P2.12 (DSEL1/SELA), RN1.14 (2)
unnamed: IC2.24 (FLAG), IC15.2 (O)
unnamed: P2.14 (DSEL2/SELB), RN1.13 (2)
unnamed: IC6.6 (O), IC14.5 (I)
unnamed: P2.22 (WRDATA), RN1.12 (2)
unnamed: P2.24 (WRGATE), RN1.11 (2)
unnamed: P2.18 (DIR), RN1.9 (2)
unnamed: P2.20 (STEP), R9.2
unnamed: IC4.1 (A), JP8.2
unnamed: IC13.3 (I), IC16.9 (Y1), RN3.7
unnamed: IC13.13 (I), IC16.3 (Y4), RN3.8
unnamed: IC9.11 (O), JP7.1
unnamed: JP10.1, P2.16 (MOTORON/MTRA), RN1.10 (2)
PHI2: IC2.25 (PHI2), IC5.13 (B), IC9.5 (I1), JP5.3, P1.C26 (PHI2)
PWRLED: IC2.7 (PA5), IC14.1 (I)
R/-W: IC1.2 (R/-W), IC2.22 (R/-W), IC5.14 (A), IC18.1 (DIR), P1.C25 (R/-W)
SELA: IC7.6 (A5), IC9.12 (I0), IC9.13 (I1), IC17.6 (Q5)
SELB: IC7.2 (A1), IC10.13 (I), IC17.2 (Q1)
SIDE0: IC2.2 (PA0), IC13.9 (I)
SLOWCLK: IC14.10 (O), IC15.11 (I), RN3.2, X1.4
STEP: IC1.16 (STEP), IC10.1 (I)
UNIT0: IC2.6 (PA4), JP3.2
UNIT1: IC2.5 (PA3), JP3.4
VCC: C1.+, C2.1, C3.1, C4.1, C5.1, C6.1, C7.1, C8.1, C9.1, C10.2, C11.2, C12.2, C13.2, C14.2, C15.2, C16.2, C17.2, C19.2, C20.2, C21.2, IC1.15 (VCC), IC2.20 (VCC), IC3.6 (G1), IC3.16 (VCC), IC4.6 (G1), IC4.16 (VCC), IC5.16 (VCC), IC6.14 (VCC), IC7.1 (DIR), IC7.20 (VCC), IC8.2 (P0), IC8.3 (Q0), IC8.12 (Q7), IC8.16 (Q3), IC8.18 (Q1), IC8.20 (VCC), IC9.14 (VCC), IC10.14 (VCC), IC11.14 (VCC), IC12.14 (VCC), IC13.14 (VCC), IC14.14 (VCC), IC15.14 (VCC), IC16.20 (VCC), IC17.20 (VCC), IC18.20 (VCC), JP1.3, JP9.8, LED1.A, LED2.A, P1.C2 (VCC), P1.C3 (VCC2), QG1.14 (VDD), R3.1, R4.2, R5.2, R6.2, R7.2, R8.2, R11.2, RN3.1
WDCSEL: IC9.3 (O), IC9.4 (I0)
WD_DRQ: IC1.27 (DRQ), IC7.8 (A7)
WD_INTR: IC1.28 (INTRQ), IC7.9 (A8)
WRDATA: IC1.22 (WD), IC10.9 (I)
WRGATE: IC1.21 (WG), IC10.5 (I)

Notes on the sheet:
CSA Floppy I/O (incl VC1581 IEC)
(C) A. Fachat
CSA-DRVIO-V1.1A-20211022
Red
Green
$4xxx
$6xxx
$E8Ax-$E8Bx
$E8Ex-$E8Fx
JP5: 2-3 installed for WD1770
VC1581 (always on)
JP6: 2-3=DD/HD
1-2=DD (VC1581)
$E8A8-F/$E8E8-F
$E8Bx/$E8Fx
Note for VC1581:
$E8A0-7/$E8E0-7
1.0C: - connect HDENS on floppy connector - power network in layout
1.1A: - remove IR output - fix pullups in Floppy interface - add own 16MHz oscillator - add data bus driver - re-org control port, fix polarity for /SELx and /MTRx - new layout
